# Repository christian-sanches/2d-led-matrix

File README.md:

# 2D LED Matrix (ESP8266 NodeMCU)

Firmware for a fixed 8×8 RGB matrix driven by an ESP8266 NodeMCU, a MicroSD
module, an IR receiver, and one active-low power button. The firmware target is
**PlatformIO `nodemcuv2` / ESP8266**. Wi-Fi is only an optional menu-controlled
radio toggle; no network service is started. No physical validation is claimed.

## Pinout

| Function | NodeMCU label | ESP8266 GPIO | Notes |
| --- | --- | ---: | --- |
| Matrix data | D2 | GPIO4 | Through a 5V-compatible level shifter recommended for 5V strips |
| Button | D1 | GPIO5 | Momentary switch between pin and GND; internal pull-up |
| IR receiver OUT | D3 | GPIO0 | Idle must remain HIGH; GPIO0 is a boot-strap pin |
| SD chip select | D8 | GPIO15 | Also a boot-strap pin; keep SD module wiring compatible with boot |
| SD SCK | D5 | GPIO14 | ESP8266 HSPI clock |
| SD MISO | D6 | GPIO12 | ESP8266 HSPI input |
| SD MOSI | D7 | GPIO13 | ESP8266 HSPI output |
| SD / IR logic supply | 3V3 | — | Only if the particular module is rated for 3.3V |

The SD module must be compatible with ESP8266 3.3V logic. Verify its voltage
requirements; some SD breakout boards include regulators/level shifting and
some do not. Keep the SD card chip-select and SPI wiring as listed.

### Matrix power and signal safety

- Identify the exact matrix/LED type and its voltage/current requirements
  before connecting it. Use a separate, regulated supply sized for the actual
  matrix and a fuse/current limit appropriate to the hardware.
- **Do not power the matrix from the NodeMCU 3.3V pin.** Connect matrix supply
  ground, NodeMCU ground, and peripheral grounds together (common ground).
- A 5V WS2812-style matrix may not reliably recognize a 3.3V ESP8266 data
  signal. A 5V-compatible logic level shifter on the GPIO4 data line is
  recommended. Confirm the strip input voltage/timing specification.
- The wiring drawing is a pinout guide, not a reviewed power design. Verify the
  module/connector pin labels and polarity before applying power.

## Build and upload

Install [PlatformIO Core](https://docs.platformio.org/en/latest/core/installation/index.html),
connect the board, then run:

```sh
pio run -e nodemcuv2
pio run -e nodemcuv2 -t upload
pio device monitor -b 115200
```

The upload port is intentionally not fixed in `platformio.ini`; PlatformIO
should discover it, or pass `--upload-port <your-port>` explicitly.

The GPIO4 output uses `NeoEsp8266BitBangWs2812xMethod` because the default ESP8266
DMA method ignores the requested pin and transmits on GPIO3/RX. Bit-bang is the
NeoPixelBus method that honors GPIO4, but it is timing-sensitive and is not the
recommended ESP8266 hardware method. It occupies roughly 1.9 ms to transmit 64
pixels and may mask IR receiver edges during that interval; IR reception and
pixel signal integrity must be checked on the actual hardware. Wi-Fi remains
off unless deliberately enabled from the menu, which only enables station radio
mode and immediately disconnects. Do not treat compile success as electrical
or timing validation.

## SD preset files

Place valid files directly in `/PRESETS` on the SD card (FAT filesystem). The
firmware discovers `.dat` files, rejects invalid files, sorts valid paths in
bytewise filename order, and cycles through that order. At most 32 valid
presets are retained; full paths must fit in 63 bytes (54 filename bytes after
`/PRESETS/`). Playback starts at 30 FPS and is menu-adjustable with presets at
15, 24, 30, 48, and 60 FPS; DAT v1 has no per-frame timing.

Each frame is exactly 192 bytes: 64 row-major RGB888 pixels, starting at the
logical top-left and proceeding across each row to the bottom-right. Serpentine
physical wiring is handled only by the firmware display driver. The header, if
present, is excluded from the frame payload.

### Legacy `.dat`

Raw RGB bytes, with a non-zero total length that is an exact multiple of 192.

### Versioned DAT v1

Exactly 20 header bytes followed by `frameCount` × 192 payload bytes:

| Bytes | Value |
| --- | --- |
| 0–7 | ASCII `LEDMAT\r\n` (`4c 45 44 4d 41 54 0d 0a`) |
| 8 | Version `1` |
| 9 | Header size `20` |
| 10 | Width `8` |
| 11 | Height `8` |
| 12 | Pixel format `1` (RGB888) |
| 13 | Flags `0` |
| 14–15 | Frame bytes `192`, unsigned little-endian |
| 16–19 | Positive frame count, unsigned little-endian |

The file length must equal `20 + frameCount * 192` exactly. A matching v1
signature with an invalid, unknown, truncated, or inconsistent header is
rejected; it is never retried as legacy data. Legacy playback remains supported.

## Controls

- The physical button toggles logical power. It is debounced in firmware; it
  does not disconnect supply power.
- IR actions support power toggle, brightness up/down, previous/next preset,
  and solid red/green/blue/white. Solid mode stays selected until previous or
  next preset is requested, or it is disabled from the menu. Brightness changes
  scale the original RGB values, so successive adjustments do not compound
  rounding.
- NEC button codes are remote-specific and **not known or hardware-verified**.
  The default map is deliberately disabled (all values zero), rather than
  guessing codes. Open the serial monitor at 115200 baud and press remote keys;
  firmware prints `protocol-id`, bit count, full value, address, and command.
  Copy each observed full `value=0x...` into the matching `IR_COMMAND_*` entry
  in `include/IRKeymap.h` (as `0x...ULL`); use unique values. After rebuilding,
  verify every mapped action with the actual remote. Protocol id is diagnostic;
  this keymap currently compares full decoded values.
- The 8×8 menu uses a separate set of configurable NEC codes in
  `include/IRKeymap.h`: `IR_COMMAND_MENU`, `IR_COMMAND_MENU_UP`,
  `IR_COMMAND_MENU_DOWN`, `IR_COMMAND_MENU_SELECT`, and
  `IR_COMMAND_MENU_BACK`. They are all zero/disabled by default. Capture the
  actual full values as above, assign each a unique `0x...ULL` value, and keep
  these codes distinct from the application-action codes. No remote key values
  are assumed by the firmware. The physical button remains a short-press
  logical power toggle; it is not a menu key and has no long-press behavior.
- The menu has four pages in this order: brightness, Wi-Fi, solid color, and
  FPS. Each page scrolls a readable mixed-case label with digits and basic
  symbols from right to left in normal reading order; the serial monitor also
  prints the page name. Brightness is shown as a percentage. The
  remaining row shows a brightness or FPS bar, Wi-Fi status, or the selected
  color swatch.
- Text rendering is reusable in `lib/BitmapText`: letters use a 4×5 mixed-case
  bitmap font while digits keep their compact 3×5 glyphs. The non-blocking
  `BitmapTextScroller` advances one pixel per configurable interval; the menu
  defaults to 100 ms and exposes `setScrollIntervalMs()`.
- Select enters brightness/color editing; Up/Down changes brightness in
  16-point steps or cycles the eight-color palette (red, green, blue, yellow,
  cyan, magenta, white, amber). Select in color editing toggles solid mode.
  Select on Wi-Fi toggles the radio. **Each Select click on the FPS page cycles
  15 → 24 → 30 → 48 → 60 → 15 FPS**, and the numeric value scrolls across the
  matrix. Each value change temporarily shows only the current value for 3
  seconds after the last change, then resumes the full label from its previous
  scroll position. Back leaves editing or exits at the root; Menu also exits.
  Power is intentionally not a menu page: the physical button and mapped IR
  power action still control it.
- Settings are volatile; none are written to flash or SD. Wi-Fi enable selects
  station radio mode and explicitly disconnects; it does not connect to an AP
  or start an AP, server, or provisioning flow. Wi-Fi defaults off at startup.
- With no input, the menu exits after 7 seconds (bounded to 5–10 seconds by the
  module) and restores the current content. Animation advancement pauses while
  the overlay is open and resumes from its retained player state. A recognized
  app control or button action while the menu is open also resets the inactivity
  timer.
- Startup brightness is limited to 96/255 to reduce initial load; adjust the
  external supply and increase brightness only after verifying the matrix's
  power/current specification.

IR is polled while the logical power is off, so a mapped power command can wake
the matrix; menu navigation remains processable while off, though it is not
visible until power is restored. Because LED data output can briefly block
interrupts on ESP8266, verify the IR receiver still decodes reliably during
animation playback.

## Diagrams and validation status

- [`simulation/wokwi`](simulation/wokwi) is a separate interactive Wokwi project
  for the menu, matrix, button, IR remote, and SD preset flow. It uses an ESP32
  compatibility target because Wokwi does not emulate the production ESP8266;
  it reuses the shared application modules but does not validate ESP8266
  electrical timing or power behavior. See its README for setup and controls.
- [`diagram.mermaid`](diagram.mermaid), [`2d-led-matrix.kicad_sch`](2d-led-matrix.kicad_sch),
  and [`kicad_schematic_project.kicad_sch`](kicad_schematic_project.kicad_sch)
  describe the ESP8266 pinout; the KiCad files are draft connector-level guides,
  not ERC-checked/validated power schematics.
- [`diagram.json`](diagram.json) and [`wokwi.toml`](wokwi.toml) are retained as
  an **old ESP32 simulation mockup**. Their board, pins, and simulated power
  wiring do not represent this ESP8266 build and must not be used as its wiring
  reference.
- No hardware photographs are included; no hardware image has been supplied
  or verified for this repository.

## Checks

Run host-testable logic checks and the ESP8266 compile:

```sh
./test/run_host_tests.sh
pio run -e nodemcuv2
```

The host tests cover all 64 unique serpentine indices, logical RGB placement,
legacy and v1 parsing/rejections, overflow checks, frame-loop offsets, control
state/brightness/solid mode, application and menu IR mapping, button debounce,
and menu navigation/settings/timeout/rendering. They do not run Arduino/SD/
display/IR/Wi-Fi hardware integration.

### Hands-on validation still required

- Confirm the exact matrix type, its supply voltage/current, connector
  orientation, color order, and top-left/serpentine direction.
- Check the GPIO4 signal with the actual level shifter/strip and verify all
  pixels and RGB placement at safe brightness.
- Test power-up/boot with the SD module on GPIO15 and IR output on GPIO0.
- Test SD initialization, malformed-file rejection, preset ordering and
  previous/next on the target card/module.
- Capture the actual remote NEC values, configure the keymap, then verify all
  actions, menu navigation, power-off wake, and IR reliability while frames
  are transmitting.
- Verify menu brightness and FPS effects, solid-color preview/resume, menu
  power behavior, and Wi-Fi radio-only toggling without AP association or
  network services.
- Confirm button behavior and debounce with the physical switch.

Until these are performed, hardware compatibility and runtime behavior remain
unverified.

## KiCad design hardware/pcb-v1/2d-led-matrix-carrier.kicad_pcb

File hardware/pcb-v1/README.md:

# 2D LED Matrix — carrier PCB v1

Design notes for the KiCad carrier board. Schematic and PCB are ERC/DRC clean; the remaining items are the two physical confirmations at the end of this file. Do not order fabrication until they are answered.

## Mechanical target

- PCB outline: 70 × 90 mm (matching the current perfboard).
- Four M3 clearance holes are planned 3.5 mm in from the board corners, matching the mounting style of the perfboard.
- Controller: LoLin-style NodeMCU ESP8266, 30 pins (2 × 15), 2.54 mm pitch, 27.94 mm row spacing; micro-USB at the lower edge, antenna toward the upper edge.
- SD breakout: directly plugged into a project-local 1 × 6 female socket, 2.54 mm pitch. It is oriented with the card slot toward the upper board edge; the carrier silk labels the header pads `CS, SCK, MOSI, MISO, VCC, GND` from left to right as photographed.
- IR receiver: remote 3-wire lead to a clearly labelled 3-pin 2.54 mm header; use signal names, not wire colors.
- LED matrix: existing red/green/white lead terminates at a 3-position high-current connector.

## Firmware-matched connections

| Function | NodeMCU pad | Net / connector |
|---|---|---|
| Matrix data | D2 / GPIO4 | 74AHCT1G125 input → 330 Ω → `LED_DATA` |
| Button | D1 / GPIO5 | `BTN` to momentary switch; other side to GND |
| IR signal | D3 / GPIO0 | `IR_SIG` |
| SD CS | D8 / GPIO15 | `SD_CS` |
| SD SCK | D5 / GPIO14 | `SD_SCK` |
| SD MISO | D6 / GPIO12 | `SD_MISO` |
| SD MOSI | D7 / GPIO13 | `SD_MOSI` |

SD module header order as viewed in the supplied photo, left to right: `CS, SCK, MOSI, MISO, VCC, GND`.

Matrix harness order as supplied by the user: red = +5 V, green = DATA, white = GND. The PCB connector will be silk-labelled `+5V / DATA / GND`.

IR connector will be silk-labelled `SIG / 3V3 / GND`; user wire colors are not assumed.

## Power and protection plan

- External 5 V supply for the LED matrix, recommended 5 V / 5 A. It feeds only J7, the matrix terminal J6, the level shifter U2, the bulk/bypass capacitors and the optional 5 V SD setting. It does **not** feed the NodeMCU.
- The NodeMCU is powered by its own micro-USB connection. `+3V3` on this board is an **output** from the NodeMCU (J2.6), distributed to the IR header and — through JP1 — to the microSD module. `VIN` (J1.15) and `VU` (J1.3) are intentionally unconnected.
- Common ground between external supply, matrix, NodeMCU, SD breakout, and IR receiver.
- JP1 selects the SD module supply: jumper **1–2 = 3V3** (the tested configuration) or **2–3 = 5V** for a 5 V-tolerant module. Fit the jumper only after checking the module.
- SN74AHCT1G125DBVR (SOT-23-5), powered from external +5 V for reliable 3.3 V-to-5 V NeoPixel data translation; 100 nF local bypass capacitor.
- 330–470 Ω series resistor on `LED_DATA` and 500–1000 µF bulk capacitor across matrix +5 V/GND.
- High-current +5 V and GND routing to use wide copper pours/tracks and connectors rated for at least 5 A. Verify copper weight and temperature-rise assumptions before release.
- Preserve the ESP8266 boot-strap states: GPIO0/D3 high and GPIO15/D8 low at reset; keep the antenna area free of copper/components.

## Release checklist

- [x] Schematic ERC: 0 violations.
- [x] PCB DRC: 0 violations, 0 unconnected pads.
- [x] Gerbers and Excellon drill files generated in `fabrication/`; ready-to-upload archive at `2d-led-matrix-carrier-gerbers.zip`.
- [ ] Confirm physical placement/clearance of the SD breakout and card insertion path.
- [ ] Confirm whether the existing perfboard's four corner holes should be carried over and their exact centers (currently assumed 3.5 mm from each corner).
- [x] SD module VCC confirmed at 3.3 V: fit JP1 jumper between pins 1 (`3V3`) and 2 (`SD`).
- [ ] Inspect the board at 1:1 scale (print `previews/pcb-1to1.pdf`) before ordering.

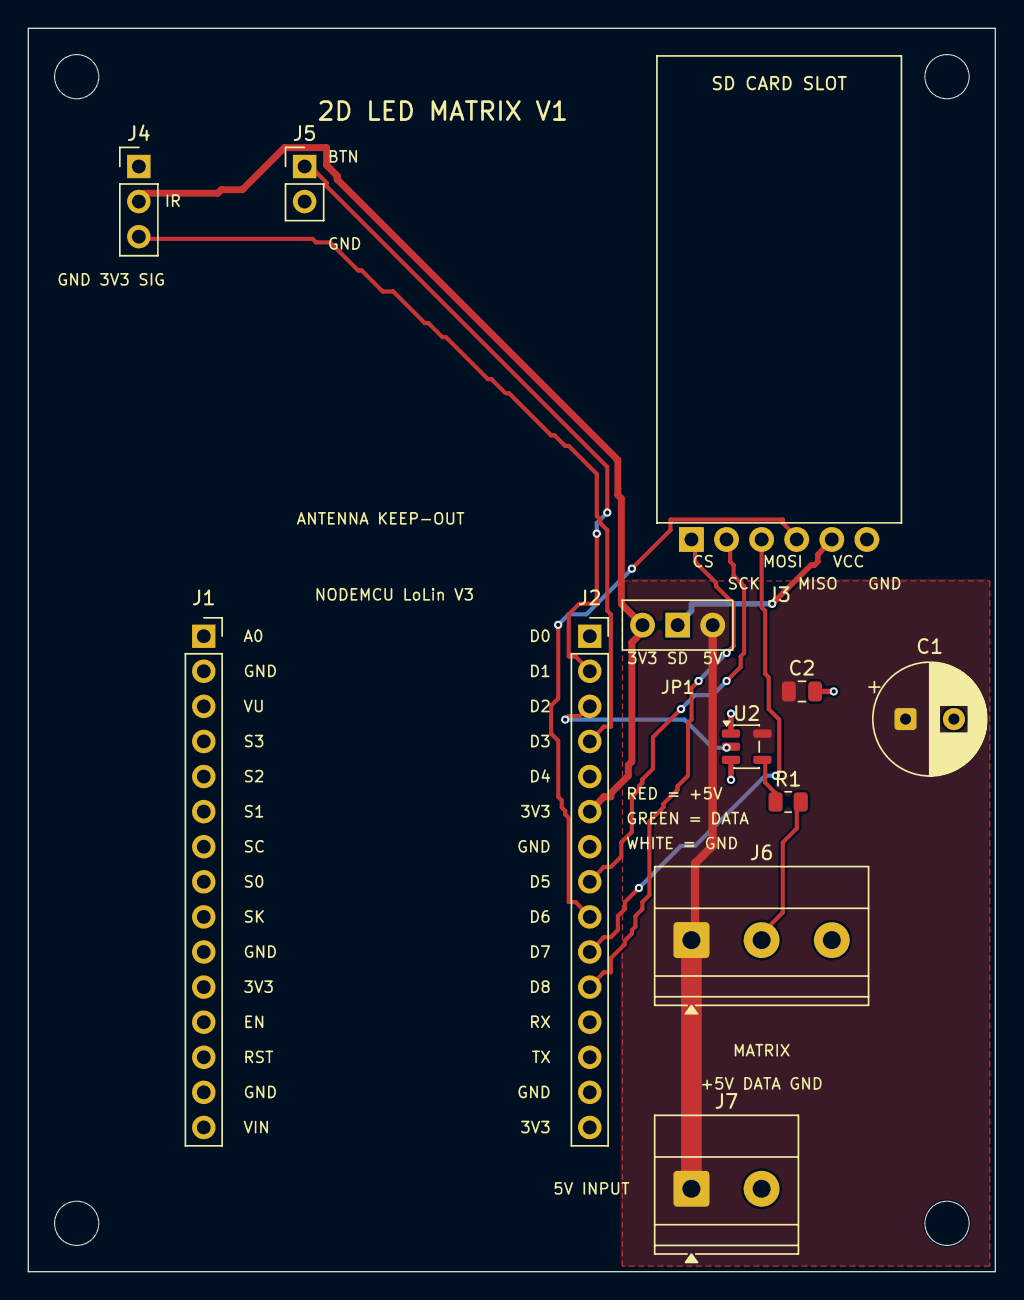
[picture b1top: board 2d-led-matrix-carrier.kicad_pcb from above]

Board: 2 copper layers, 70.0 x 90.0 mm, 16 parts (0 on the bottom side), 13 nets.

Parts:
C1: 1000uF/10V; CP_Radial_D8.0mm_P3.50mm
C2: 100nF; C_0805_2012Metric
H1, H2, H3, H4: M3; MountingHole_3.2mm_M3
J1: NodeMCU LEFT (A0-VIN); PinSocket_1x15_P2.54mm_Vertical
J2: NodeMCU RIGHT (D0-3V3); PinSocket_1x15_P2.54mm_Vertical
J3: microSD breakout; SD_Module_1x06_P2.54mm
J4: IR (GND-3V3-SIG); PinHeader_1x03_P2.54mm_Vertical
J5: Button (BTN-GND); PinHeader_1x02_P2.54mm_Vertical
J6: Matrix (+5V-DATA-GND); TerminalBlock_Phoenix_MKDS-1,5-3-5.08_1x03_P5.08mm_Horizont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
J7: +5V INPUT; TerminalBlock_Phoenix_MKDS-1,5-2-5.08_1x02_P5.08mm_Horizont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
JP1: SD VCC (3V3/5V); SD_VCC_Selector_1x03_P2.54mm
R1: 330R; R_0805_2012Metric
U2: SN74AHCT1G125DBVR; SOT-23-5

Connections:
+3V3: J2.6, J4.2, JP1.1
+5V: C1.1, C2.1, J6.1, J7.1, JP1.3, U2.5
BTN: J2.2, J5.1
GND: C1.2, C2.2, J1.2, J1.10, J1.14, J2.7, J2.14, J3.6, J4.1, J5.2, J6.3, J7.2, U2.1, U2.3
IR_SIG: J2.4, J4.3
LED_DATA: J6.2, R1.2
LED_DATA_BUF: R1.1, U2.4
LED_DATA_LV: J2.3, U2.2
SD_CS: J2.11, J3.1
SD_MISO: J2.9, J3.4
SD_MOSI: J2.10, J3.3
SD_SCK: J2.8, J3.2
SD_VCC: J3.5, JP1.2

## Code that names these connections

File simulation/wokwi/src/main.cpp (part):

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
// This pin map belongs only to the Wokwi ESP32 target. It intentionally does
// not replace the NodeMCU pin map in the real firmware.
static const uint8_t PIN_BTN = 25;
static const uint8_t PIN_IR = 26;
static const uint8_t PIN_LED_DATA = 4;
static const uint8_t PIN_SD_CS = 27;
static const uint8_t PIN_SD_SCK = 18;
static const uint8_t PIN_SD_MISO = 19;
static const uint8_t PIN_SD_MOSI = 23;

class SimulationMenuActions : public MenuActions {
public:
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    DisplayController& _display;
};

DisplayController display(PIN_LED_DATA);
AnimationController animation(PIN_SD_CS);
IRController ir(PIN_IR);
ControlState controls;
ButtonDebouncer button;
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    Serial.println(F("2D LED Matrix — Wokwi ESP32 simulation"));
    Serial.println(F("This simulates app behavior, not ESP8266 electrical timing."));

    pinMode(PIN_BTN, INPUT_PULLUP);
    SPI.begin(PIN_SD_SCK, PIN_SD_MISO, PIN_SD_MOSI, PIN_SD_CS);
    display.begin();
    display.setBrightness(controls.brightness());
    renderDiagnosticPattern();
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    const bool menuWasActive = menu.isActive();
    bool stateChanged = false;

    if (button.update(digitalRead(PIN_BTN) == HIGH, now)) {
        dispatch(ControlAction::PowerToggle);
        menu.noteActivity(now);
        stateChanged = true;
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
